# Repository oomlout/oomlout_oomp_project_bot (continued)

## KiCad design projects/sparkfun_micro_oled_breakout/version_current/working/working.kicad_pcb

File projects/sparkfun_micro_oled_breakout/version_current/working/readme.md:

# Micro_OLED_Breakout by sparkfun  
This is a harvested standardized copy of a project from github.  
The original project can be found at:  
https://github.com/sparkfun/Micro_OLED_Breakout  
Please consult that link for additional, details, files, and license information.  
Note: It was auto harvested and if the original repo had more than one board file or anything out of the ordinary the files here are likely not representative.

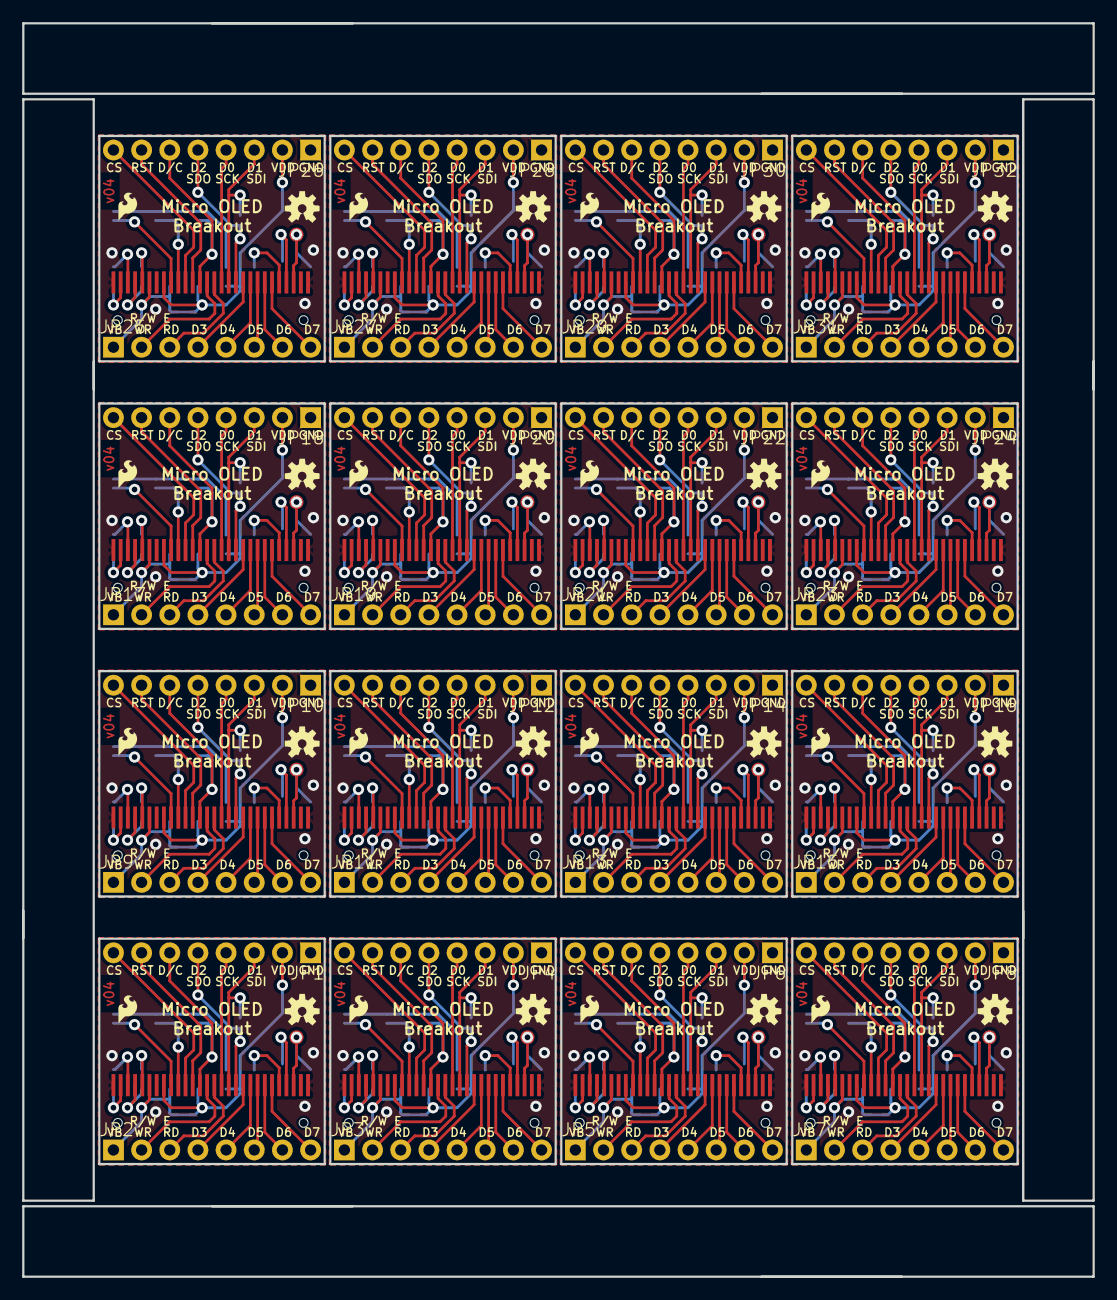
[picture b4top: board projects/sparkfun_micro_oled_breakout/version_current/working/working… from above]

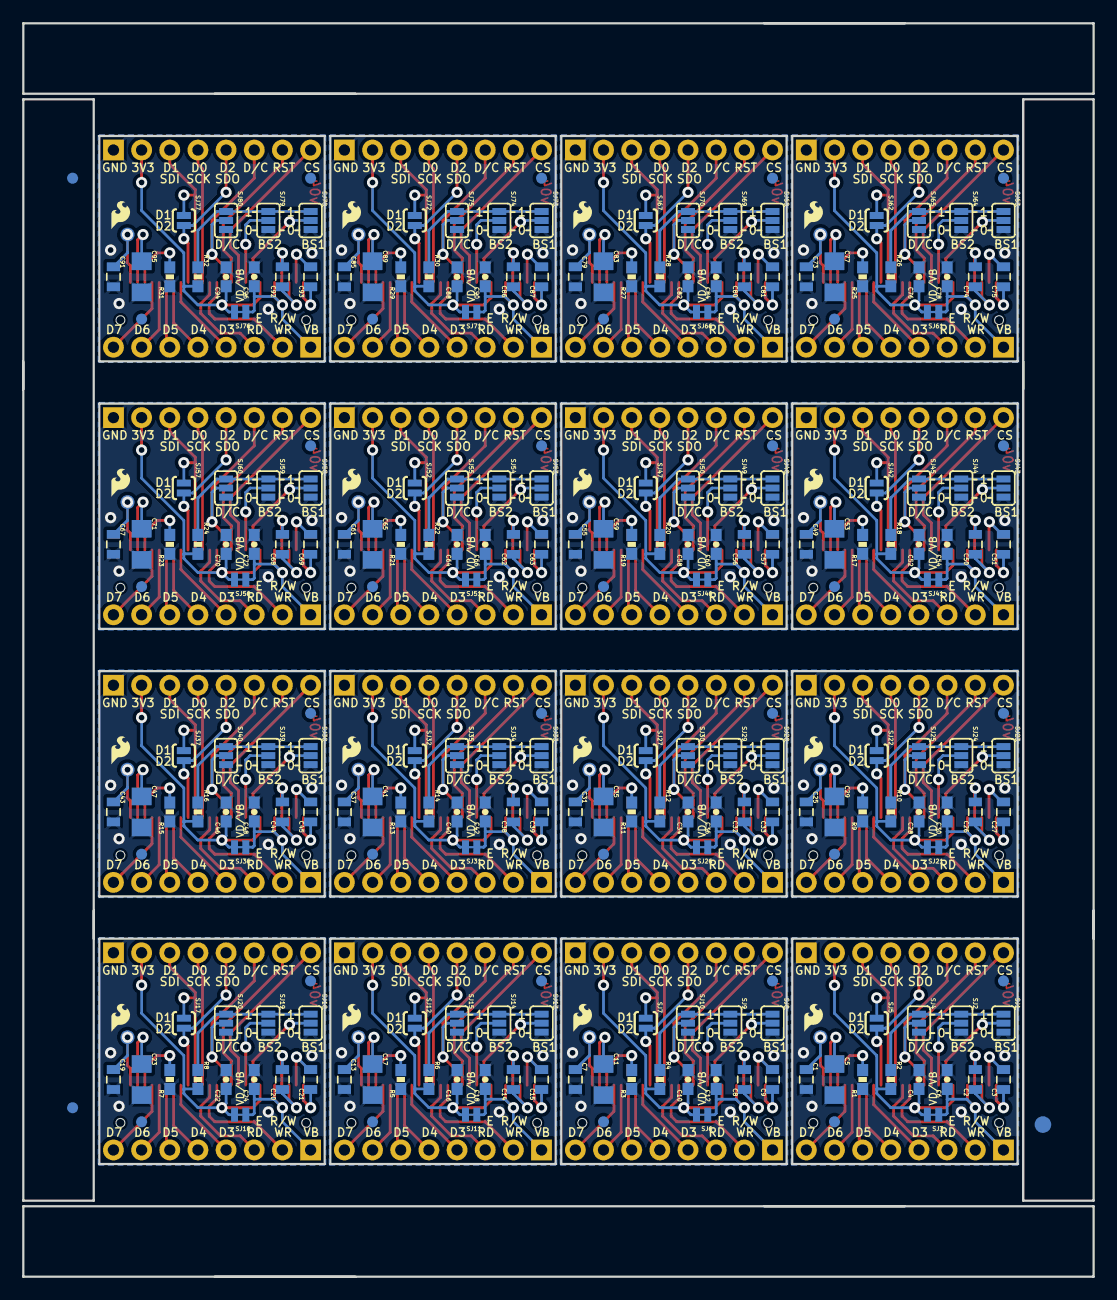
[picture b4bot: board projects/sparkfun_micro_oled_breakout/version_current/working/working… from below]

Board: 2 copper layers, 96.5 x 113.0 mm, 371 parts (275 on the bottom side), 416 nets.

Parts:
C1, C7, C13, C19, C25, C31, C37, C43, C49, C55, C61, C67, C73, C79, C85, C91: 2.2uF; 0805
C2, C3, C8, C9, C14, C15, C20, C21, C26, C27, C32, C33, C38, C39, C44, C45, C50, C51, C56, C57, C62, C63, C68, C69, C74, C75, C80, C81, C86, C87, C92, C93: 1uF X5R; 0805
C4, C6, C10, C12, C16, C18, C22, C24, C28, C30, C34, C36, C40, C42, C46, C48, C52, C54, C58, C60, C64, C66, C70, C72, C76, C78, C82, C84, C88, C90, C94, C96: 1uF; 0603-CAP
C5, C11, C17, C23, C29, C35, C41, C47, C53, C59, C65, C71, C77, C83, C89, C95: 4.7uF/16V; 1206
E$1: FIDUCIAL-1.5X3
E$4, E$8: FIDUCIAL-1X2
FID1, FID2, FID3, FID4, FID5, FID6, FID7, FID8, FID9, FID10, FID11, FID12, FID13, FID14, FID15, FID16, FID17, FID18, FID19, FID20, FID21, FID22, FID23, FID24, FID25, FID26, FID27, FID28, FID29, FID30, FID31, FID32: FIDUCIAL1X2; FIDUCIAL-1X2
JP1, JP2, JP3, JP4, JP5, JP6, JP7, JP8, JP9, JP10, JP11, JP12, JP13, JP14, JP15, JP16, JP17, JP18, JP19, JP20, JP21, JP22, JP23, JP24, JP25, JP26, JP27, JP28, JP29, JP30, JP31, JP32: 1X08_PIN1_NO_SILK
LOGO1, LOGO2, LOGO4, LOGO5, LOGO7, LOGO8, LOGO10, LOGO11, LOGO13, LOGO14, LOGO16, LOGO17, LOGO19, LOGO20, LOGO22, LOGO23, LOGO25, LOGO26, LOGO28, LOGO29, LOGO31, LOGO32, LOGO34, LOGO35, LOGO37, LOGO38, LOGO40, LOGO41, LOGO43, LOGO44, LOGO46, LOGO47: SFE_LOGO_FLAME.1_INCH; SFE_LOGO_FLAME_.1
LOGO3, LOGO6, LOGO9, LOGO12, LOGO15, LOGO18, LOGO21, LOGO24, LOGO27, LOGO30, LOGO33, LOGO36, LOGO39, LOGO42, LOGO45, LOGO48: OSHW-LOGOS; OSHW-LOGO-S
OLED1, OLED2, OLED3, OLED4, OLED5, OLED6, OLED7, OLED8, OLED9, OLED10, OLED11, OLED12, OLED13, OLED14, OLED15, OLED16: OLED0.66; OLED-0.66-64X48
R1, R3, R5, R7, R9, R11, R13, R15, R17, R19, R21, R23, R25, R27, R29, R31: 390k; 0603-RES
R2, R4, R6, R8, R10, R12, R14, R16, R18, R20, R22, R24, R26, R28, R30, R32: 10k; 0603-RES
SJ1, SJ8, SJ13, SJ18, SJ23, SJ28, SJ33, SJ38, SJ43, SJ48, SJ53, SJ58, SJ63, SJ68, SJ73, SJ78: BS1; PAD-JUMPER-3-2OF3_NC_BY_PASTE_YES_SILK_FULL_BOX
SJ2, SJ9, SJ14, SJ19, SJ24, SJ29, SJ34, SJ39, SJ44, SJ49, SJ54, SJ59, SJ64, SJ69, SJ74, SJ79: BS2; PAD-JUMPER-3-2OF3_NC_BY_PASTE_YES_SILK_FULL_BOX
SJ3, SJ6, SJ11, SJ16, SJ21, SJ26, SJ31, SJ36, SJ41, SJ46, SJ51, SJ56, SJ61, SJ66, SJ71, SJ76: PAD-JUMPER-2-NC_BY_TRACE_NO_SILK
SJ4, SJ10, SJ15, SJ20, SJ25, SJ30, SJ35, SJ40, SJ45, SJ50, SJ55, SJ60, SJ65, SJ70, SJ75, SJ80: PAD-JUMPER-3-NO-TIGHT
SJ5, SJ7, SJ12, SJ17, SJ22, SJ27, SJ32, SJ37, SJ42, SJ47, SJ52, SJ57, SJ62, SJ67, SJ72, SJ77: PAD-JUMPER-2-NO_YES_SILK
TP1, TP2, TP3, TP4, TP5, TP6, TP7, TP8, TP9, TP10, TP11, TP12, TP13, TP14, TP15, TP16, TP17, TP18, TP19, TP20, TP21, TP22, TP23, TP24, TP25, TP26, TP27, TP28, TP29, TP30, TP31, TP32: TEST-POINT3X5; PAD.03X.05

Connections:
BS1: OLED1.9, SJ1.2
BS2: OLED1.10, SJ2.2
BS3: OLED2.9, SJ8.2
BS4: OLED2.10, SJ9.2
BS5: OLED3.9, SJ13.2
BS6: OLED3.10, SJ14.2
BS7: OLED4.9, SJ18.2
BS8: OLED4.10, SJ19.2
BS9: OLED5.9, SJ23.2
BS10: OLED5.10, SJ24.2
BS11: OLED6.9, SJ28.2
BS12: OLED6.10, SJ29.2
BS13: OLED7.9, SJ33.2
BS14: OLED7.10, SJ34.2
BS15: OLED8.9, SJ38.2
BS16: OLED8.10, SJ39.2
BS17: OLED9.9, SJ43.2
BS18: OLED9.10, SJ44.2
BS19: OLED10.9, SJ48.2
BS20: OLED10.10, SJ49.2
BS21: OLED11.9, SJ53.2
BS22: OLED11.10, SJ54.2
BS23: OLED12.9, SJ58.2
BS24: OLED12.10, SJ59.2
BS25: OLED13.9, SJ63.2
BS26: OLED13.10, SJ64.2
BS27: OLED14.9, SJ68.2
BS28: OLED14.10, SJ69.2
BS29: OLED15.9, SJ73.2
BS30: OLED15.10, SJ74.2
BS31: OLED16.9, SJ78.2
BS32: OLED16.10, SJ79.2
C1N: C2.2, OLED1.5
C1N1: C8.2, OLED2.5
C1N2: C14.2, OLED3.5
C1N3: C20.2, OLED4.5
C1N4: C26.2, OLED5.5
C1N5: C32.2, OLED6.5
C1N6: C38.2, OLED7.5
C1N7: C44.2, OLED8.5
C1N8: C50.2, OLED9.5
C1N9: C56.2, OLED10.5
C1N10: C62.2, OLED11.5
C1N11: C68.2, OLED12.5
C1N12: C74.2, OLED13.5
C1N13: C80.2, OLED14.5
C1N14: C86.2, OLED15.5
C1N15: C92.2, OLED16.5
C1P: C2.1, OLED1.4
C1P1: C8.1, OLED2.4
C1P2: C14.1, OLED3.4
C1P3: C20.1, OLED4.4
C1P4: C26.1, OLED5.4
C1P5: C32.1, OLED6.4
C1P6: C38.1, OLED7.4
C1P7: C44.1, OLED8.4
C1P8: C50.1, OLED9.4
C1P9: C56.1, OLED10.4
C1P10: C62.1, OLED11.4
C1P11: C68.1, OLED12.4
C1P12: C74.1, OLED13.4
C1P13: C80.1, OLED14.4
C1P14: C86.1, OLED15.4
C1P15: C92.1, OLED16.4
C2N: C3.2, OLED1.3
C2N1: C9.2, OLED2.3
C2N2: C15.2, OLED3.3
C2N3: C21.2, OLED4.3
C2N4: C27.2, OLED5.3
C2N5: C33.2, OLED6.3
C2N6: C39.2, OLED7.3
C2N7: C45.2, OLED8.3
C2N8: C51.2, OLED9.3
C2N9: C57.2, OLED10.3
C2N10: C63.2, OLED11.3
C2N11: C69.2, OLED12.3
C2N12: C75.2, OLED13.3
C2N13: C81.2, OLED14.3
C2N14: C87.2, OLED15.3
C2N15: C93.2, OLED16.3
C2P: C3.1, OLED1.2
C2P1: C9.1, OLED2.2
C2P2: C15.1, OLED3.2
C2P3: C21.1, OLED4.2
C2P4: C27.1, OLED5.2
C2P5: C33.1, OLED6.2
C2P6: C39.1, OLED7.2
C2P7: C45.1, OLED8.2
C2P8: C51.1, OLED9.2
C2P9: C57.1, OLED10.2
C2P10: C63.1, OLED11.2
C2P11: C69.1, OLED12.2
C2P12: C75.1, OLED13.2
C2P13: C81.1, OLED14.2
C2P14: C87.1, OLED15.2
C2P15: C93.1, OLED16.2
CS: JP1.8, OLED1.11
CS1: JP4.8, OLED2.11
CS2: JP6.8, OLED3.11
CS3: JP8.8, OLED4.11
CS4: JP10.8, OLED5.11
CS5: JP12.8, OLED6.11
CS6: JP14.8, OLED7.11
CS7: JP16.8, OLED8.11
CS8: JP18.8, OLED9.11
CS9: JP20.8, OLED10.11
CS10: JP22.8, OLED11.11
CS11: JP24.8, OLED12.11
CS12: JP26.8, OLED13.11
CS13: JP28.8, OLED14.11
CS14: JP30.8, OLED15.11
CS15: JP32.8, OLED16.11
D0/SCK: JP1.4, OLED1.16
D0/SCK1: JP4.4, OLED2.16
D0/SCK2: JP6.4, OLED3.16
D0/SCK3: JP8.4, OLED4.16
D0/SCK4: JP10.4, OLED5.16
D0/SCK5: JP12.4, OLED6.16
D0/SCK6: JP14.4, OLED7.16
D0/SCK7: JP16.4, OLED8.16
D0/SCK8: JP18.4, OLED9.16
D0/SCK9: JP20.4, OLED10.16
D0/SCK10: JP22.4, OLED11.16
D0/SCK11: JP24.4, OLED12.16
D0/SCK12: JP26.4, OLED13.16
D0/SCK13: JP28.4, OLED14.16
D0/SCK14: JP30.4, OLED15.16
D0/SCK15: JP32.4, OLED16.16
D1: JP3.8, OLED2.23
D1/MOSI: JP1.3, OLED1.17, SJ5.1
D1/MOSI1: JP4.3, OLED2.17, SJ7.1
D1/MOSI2: JP6.3, OLED3.17, SJ12.1
D1/MOSI3: JP8.3, OLED4.17, SJ17.1
D1/MOSI4: JP10.3, OLED5.17, SJ22.1
D1/MOSI5: JP12.3, OLED6.17, SJ27.1
D1/MOSI6: JP14.3, OLED7.17, SJ32.1
D1/MOSI7: JP16.3, OLED8.17, SJ37.1
D1/MOSI8: JP18.3, OLED9.17, SJ42.1
D1/MOSI9: JP20.3, OLED10.17, SJ47.1
D1/MOSI10: JP22.3, OLED11.17, SJ52.1
D1/MOSI11: JP24.3, OLED12.17, SJ57.1
D1/MOSI12: JP26.3, OLED13.17, SJ62.1
D1/MOSI13: JP28.3, OLED14.17, SJ67.1
D1/MOSI14: JP30.3, OLED15.17, SJ72.1
D1/MOSI15: JP32.3, OLED16.17, SJ77.1
D2: JP1.5, OLED1.18, SJ5.2
D3: JP2.4, OLED1.19
D4: JP2.5, OLED1.20
D5: JP2.6, OLED1.21
D6: JP2.7, OLED1.22
D7: JP2.8, OLED1.23
D8: JP3.7, OLED2.22
D9: JP3.6, OLED2.21
D10: JP3.5, OLED2.20
D11: JP3.4, OLED2.19
D12: JP4.5, OLED2.18, SJ7.2
D13: JP5.8, OLED3.23
D14: JP5.7, OLED3.22
D15: JP5.6, OLED3.21
D16: JP5.5, OLED3.20
D17: JP5.4, OLED3.19
D18: JP6.5, OLED3.18, SJ12.2
D19: JP7.8, OLED4.23
D20: JP7.7, OLED4.22
D21: JP7.6, OLED4.21
D22: JP7.5, OLED4.20
D23: JP7.4, OLED4.19
D24: JP8.5, OLED4.18, SJ17.2
D25: JP9.8, OLED5.23
D26: JP9.7, OLED5.22
D27: JP9.6, OLED5.21
D28: JP9.5, OLED5.20
D29: JP9.4, OLED5.19
D30: JP10.5, OLED5.18, SJ22.2
D31: JP11.8, OLED6.23
D32: JP11.7, OLED6.22
D33: JP11.6, OLED6.21
D34: JP11.5, OLED6.20
D35: JP11.4, OLED6.19
D36: JP12.5, OLED6.18, SJ27.2
D37: JP13.8, OLED7.23
D38: JP13.7, OLED7.22
D39: JP13.6, OLED7.21
D40: JP13.5, OLED7.20
D41: JP13.4, OLED7.19
D42: JP14.5, OLED7.18, SJ32.2
D43: JP15.8, OLED8.23
D44: JP15.7, OLED8.22
D45: JP15.6, OLED8.21
D46: JP15.5, OLED8.20
D47: JP15.4, OLED8.19
D48: JP16.5, OLED8.18, SJ37.2
D49: JP17.8, OLED9.23
D50: JP17.7, OLED9.22
D51: JP17.6, OLED9.21
D52: JP17.5, OLED9.20
D53: JP17.4, OLED9.19
D54: JP18.5, OLED9.18, SJ42.2
D55: JP19.8, OLED10.23
D56: JP19.7, OLED10.22
D57: JP19.6, OLED10.21
D58: JP19.5, OLED10.20
D59: JP19.4, OLED10.19
D60: JP20.5, OLED10.18, SJ47.2
D61: JP21.8, OLED11.23
D62: JP21.7, OLED11.22
D63: JP21.6, OLED11.21
D64: JP21.5, OLED11.20
D65: JP21.4, OLED11.19
D66: JP22.5, OLED11.18, SJ52.2
D67: JP23.8, OLED12.23
D68: JP23.7, OLED12.22
D69: JP23.6, OLED12.21
D70: JP23.5, OLED12.20
D71: JP23.4, OLED12.19
D72: JP24.5, OLED12.18, SJ57.2
D73: JP25.8, OLED13.23
D74: JP25.7, OLED13.22
D75: JP25.6, OLED13.21
D76: JP25.5, OLED13.20
D77: JP25.4, OLED13.19
D78: JP26.5, OLED13.18, SJ62.2
D79: JP27.8, OLED14.23
D80: JP27.7, OLED14.22
D81: JP27.6, OLED14.21
D82: JP27.5, OLED14.20
D83: JP27.4, OLED14.19
D84: JP28.5, OLED14.18, SJ67.2
D85: JP29.8, OLED15.23
D86: JP29.7, OLED15.22
D87: JP29.6, OLED15.21
D88: JP29.5, OLED15.20
D89: JP29.4, OLED15.19
D90: JP30.5, OLED15.18, SJ72.2
D91: JP31.8, OLED16.23
D92: JP31.7, OLED16.22
D93: JP31.6, OLED16.21
D94: JP31.5, OLED16.20
D95: JP31.4, OLED16.19
D96: JP32.5, OLED16.18, SJ77.2
D/C: JP1.6, OLED1.13, SJ4.2
D/C1: JP4.6, OLED2.13, SJ10.2
D/C2: JP6.6, OLED3.13, SJ15.2
D/C3: JP8.6, OLED4.13, SJ20.2
D/C4: JP10.6, OLED5.13, SJ25.2
D/C5: JP12.6, OLED6.13, SJ30.2
D/C6: JP14.6, OLED7.13, SJ35.2
D/C7: JP16.6, OLED8.13, SJ40.2
D/C8: JP18.6, OLED9.13, SJ45.2
D/C9: JP20.6, OLED10.13, SJ50.2
D/C10: JP22.6, OLED11.13, SJ55.2
D/C11: JP24.6, OLED12.13, SJ60.2
D/C12: JP26.6, OLED13.13, SJ65.2
D/C13: JP28.6, OLED14.13, SJ70.2
D/C14: JP30.6, OLED15.13, SJ75.2
D/C15: JP32.6, OLED16.13, SJ80.2
GND: C1.2, C4.2, C5.2, C6.2, JP1.1, OLED1.1, OLED1.7, OLED1.27, OLED1.28, R1.1, SJ1.3, SJ2.3, SJ4.3
GND1: C7.2, C10.2, C11.2, C12.2, JP4.1, OLED2.1, OLED2.7, OLED2.27, OLED2.28, R3.1, SJ8.3, SJ9.3, SJ10.3
GND2: C13.2, C16.2, C17.2, C18.2, JP6.1, OLED3.1, OLED3.7, OLED3.27, OLED3.28, R5.1, SJ13.3, SJ14.3, SJ15.3
GND3: C19.2, C22.2, C23.2, C24.2, JP8.1, OLED4.1, OLED4.7, OLED4.27, OLED4.28, R7.1, SJ18.3, SJ19.3, SJ20.3
GND4: C25.2, C28.2, C29.2, C30.2, JP10.1, OLED5.1, OLED5.7, OLED5.27, OLED5.28, R9.1, SJ23.3, SJ24.3, SJ25.3
GND5: C31.2, C34.2, C35.2, C36.2, JP12.1, OLED6.1, OLED6.7, OLED6.27, OLED6.28, R11.1, SJ28.3, SJ29.3, SJ30.3
GND6: C37.2, C40.2, C41.2, C42.2, JP14.1, OLED7.1, OLED7.7, OLED7.27, OLED7.28, R13.1, SJ33.3, SJ34.3, SJ35.3
GND7: C43.2, C46.2, C47.2, C48.2, JP16.1, OLED8.1, OLED8.7, OLED8.27, OLED8.28, R15.1, SJ38.3, SJ39.3, SJ40.3
GND8: C49.2, C52.2, C53.2, C54.2, JP18.1, OLED9.1, OLED9.7, OLED9.27, OLED9.28, R17.1, SJ43.3, SJ44.3, SJ45.3
GND9: C55.2, C58.2, C59.2, C60.2, JP20.1, OLED10.1, OLED10.7, OLED10.27, OLED10.28, R19.1, SJ48.3, SJ49.3, SJ50.3
GND10: C61.2, C64.2, C65.2, C66.2, JP22.1, OLED11.1, OLED11.7, OLED11.27, OLED11.28, R21.1, SJ53.3, SJ54.3, SJ55.3
GND11: C67.2, C70.2, C71.2, C72.2, JP24.1, OLED12.1, OLED12.7, OLED12.27, OLED12.28, R23.1, SJ58.3, SJ59.3, SJ60.3
GND12: C73.2, C76.2, C77.2, C78.2, JP26.1, OLED13.1, OLED13.7, OLED13.27, OLED13.28, R25.1, SJ63.3, SJ64.3, SJ65.3
GND13: C79.2, C82.2, C83.2, C84.2, JP28.1, OLED14.1, OLED14.7, OLED14.27, OLED14.28, R27.1, SJ68.3, SJ69.3, SJ70.3
GND14: C85.2, C88.2, C89.2, C90.2, JP30.1, OLED15.1, OLED15.7, OLED15.27, OLED15.28, R29.1, SJ73.3, SJ74.3, SJ75.3
GND15: C91.2, C94.2, C95.2, C96.2, JP32.1, OLED16.1, OLED16.7, OLED16.27, OLED16.28, R31.1, SJ78.3, SJ79.3, SJ80.3
IREF: OLED1.24, R1.2
IREF1: OLED2.24, R3.2
IREF2: OLED3.24, R5.2
IREF3: OLED4.24, R7.2
IREF4: OLED5.24, R9.2
IREF5: OLED6.24, R11.2
IREF6: OLED7.24, R13.2
IREF7: OLED8.24, R15.2
IREF8: OLED9.24, R17.2
IREF9: OLED10.24, R19.2
IREF10: OLED11.24, R21.2
IREF11: OLED12.24, R23.2
IREF12: OLED13.24, R25.2
IREF13: OLED14.24, R27.2
IREF14: OLED15.24, R29.2
IREF15: OLED16.24, R31.2
RD/E: JP2.3, OLED1.15
RD/E1: JP3.3, OLED2.15
RD/E2: JP5.3, OLED3.15
RD/E3: JP7.3, OLED4.15
RD/E4: JP9.3, OLED5.15
RD/E5: JP11.3, OLED6.15
RD/E6: JP13.3, OLED7.15
RD/E7: JP15.3, OLED8.15
RD/E8: JP17.3, OLED9.15
RD/E9: JP19.3, OLED10.15
RD/E10: JP21.3, OLED11.15
RD/E11: JP23.3, OLED12.15
RD/E12: JP25.3, OLED13.15
RD/E13: JP27.3, OLED14.15
RD/E14: JP29.3, OLED15.15
RD/E15: JP31.3, OLED16.15
RESET: JP1.7, OLED1.12
RESET1: JP4.7, OLED2.12
RESET2: JP6.7, OLED3.12
RESET3: JP8.7, OLED4.12
RESET4: JP10.7, OLED5.12
RESET5: JP12.7, OLED6.12
RESET6: JP14.7, OLED7.12
RESET7: JP16.7, OLED8.12
RESET8: JP18.7, OLED9.12
RESET9: JP20.7, OLED10.12
RESET10: JP22.7, OLED11.12
RESET11: JP24.7, OLED12.12
RESET12: JP26.7, OLED13.12
RESET13: JP28.7, OLED14.12
RESET14: JP30.7, OLED15.12
RESET15: JP32.7, OLED16.12
VBAT: C6.1, JP2.1, OLED1.6, SJ3.1
VBAT1: C12.1, JP3.1, OLED2.6, SJ6.1
VBAT2: C18.1, JP5.1, OLED3.6, SJ11.1
VBAT3: C24.1, JP7.1, OLED4.6, SJ16.1
VBAT4: C30.1, JP9.1, OLED5.6, SJ21.1
VBAT5: C36.1, JP11.1, OLED6.6, SJ26.1
VBAT6: C42.1, JP13.1, OLED7.6, SJ31.1
VBAT7: C48.1, JP15.1, OLED8.6, SJ36.1
VBAT8: C54.1, JP17.1, OLED9.6, SJ41.1
VBAT9: C60.1, JP19.1, OLED10.6, SJ46.1
VBAT10: C66.1, JP21.1, OLED11.6, SJ51.1
VBAT11: C72.1, JP23.1, OLED12.6, SJ56.1
VBAT12: C78.1, JP25.1, OLED13.6, SJ61.1
VBAT13: C84.1, JP27.1, OLED14.6, SJ66.1
VBAT14: C90.1, JP29.1, OLED15.6, SJ71.1
VBAT15: C96.1, JP31.1, OLED16.6, SJ76.1
VCC: C1.1, OLED1.26, TP1.P$1, TP2.P$1
VCC1: C7.1, OLED2.26, TP3.P$1, TP4.P$1
VCC2: C13.1, OLED3.26, TP5.P$1, TP6.P$1
VCC3: C19.1, OLED4.26, TP7.P$1, TP8.P$1
VCC4: C25.1, OLED5.26, TP9.P$1, TP10.P$1
VCC5: C31.1, OLED6.26, TP11.P$1, TP12.P$1
VCC6: C37.1, OLED7.26, TP13.P$1, TP14.P$1
VCC7: C43.1, OLED8.26, TP15.P$1, TP16.P$1
VCC8: C49.1, OLED9.26, TP17.P$1, TP18.P$1
VCC9: C55.1, OLED10.26, TP19.P$1, TP20.P$1
VCC10: C61.1, OLED11.26, TP21.P$1, TP22.P$1
VCC11: C67.1, OLED12.26, TP23.P$1, TP24.P$1
VCC12: C73.1, OLED13.26, TP25.P$1, TP26.P$1
VCC13: C79.1, OLED14.26, TP27.P$1, TP28.P$1
VCC14: C85.1, OLED15.26, TP29.P$1, TP30.P$1
VCC15: C91.1, OLED16.26, TP31.P$1, TP32.P$1
VCOMH: C5.1, OLED1.25
VCOMH1: C11.1, OLED2.25
VCOMH2: C17.1, OLED3.25
VCOMH3: C23.1, OLED4.25
VCOMH4: C29.1, OLED5.25
VCOMH5: C35.1, OLED6.25
VCOMH6: C41.1, OLED7.25
VCOMH7: C47.1, OLED8.25
VCOMH8: C53.1, OLED9.25
VCOMH9: C59.1, OLED10.25
VCOMH10: C65.1, OLED11.25
VCOMH11: C71.1, OLED12.25
VCOMH12: C77.1, OLED13.25
VCOMH13: C83.1, OLED14.25
VCOMH14: C89.1, OLED15.25
VCOMH15: C95.1, OLED16.25
VDD: C4.1, JP1.2, OLED1.8, R2.2, SJ3.2
VDD1: C10.1, JP4.2, OLED2.8, R4.2, SJ6.2
VDD2: C16.1, JP6.2, OLED3.8, R6.2, SJ11.2
VDD3: C22.1, JP8.2, OLED4.8, R8.2, SJ16.2
VDD4: C28.1, JP10.2, OLED5.8, R10.2, SJ21.2
VDD5: C34.1, JP12.2, OLED6.8, R12.2, SJ26.2
VDD6: C40.1, JP14.2, OLED7.8, R14.2, SJ31.2
VDD7: C46.1, JP16.2, OLED8.8, R16.2, SJ36.2
VDD8: C52.1, JP18.2, OLED9.8, R18.2, SJ41.2
VDD9: C58.1, JP20.2, OLED10.8, R20.2, SJ46.2
VDD10: C64.1, JP22.2, OLED11.8, R22.2, SJ51.2
VDD11: C70.1, JP24.2, OLED12.8, R24.2, SJ56.2
VDD12: C76.1, JP26.2, OLED13.8, R26.2, SJ61.2
VDD13: C82.1, JP28.2, OLED14.8, R28.2, SJ66.2
VDD14: C88.1, JP30.2, OLED15.8, R30.2, SJ71.2
VDD15: C94.1, JP32.2, OLED16.8, R32.2, SJ76.2
VDD_PU: R2.1, SJ1.1, SJ2.1, SJ4.1
VDD_PU1: R4.1, SJ8.1, SJ9.1, SJ10.1
VDD_PU2: R6.1, SJ13.1, SJ14.1, SJ15.1
VDD_PU3: R8.1, SJ18.1, SJ19.1, SJ20.1
VDD_PU4: R10.1, SJ23.1, SJ24.1, SJ25.1
VDD_PU5: R12.1, SJ28.1, SJ29.1, SJ30.1
VDD_PU6: R14.1, SJ33.1, SJ34.1, SJ35.1
VDD_PU7: R16.1, SJ38.1, SJ39.1, SJ40.1
VDD_PU8: R18.1, SJ43.1, SJ44.1, SJ45.1
VDD_PU9: R20.1, SJ48.1, SJ49.1, SJ50.1
VDD_PU10: R22.1, SJ53.1, SJ54.1, SJ55.1
VDD_PU11: R24.1, SJ58.1, SJ59.1, SJ60.1
VDD_PU12: R26.1, SJ63.1, SJ64.1, SJ65.1
VDD_PU13: R28.1, SJ68.1, SJ69.1, SJ70.1
VDD_PU14: R30.1, SJ73.1, SJ74.1, SJ75.1
VDD_PU15: R32.1, SJ78.1, SJ79.1, SJ80.1
WR/RW: JP2.2, OLED1.14
WR/RW1: JP3.2, OLED2.14
WR/RW2: JP5.2, OLED3.14
WR/RW3: JP7.2, OLED4.14
WR/RW4: JP9.2, OLED5.14
WR/RW5: JP11.2, OLED6.14
WR/RW6: JP13.2, OLED7.14
WR/RW7: JP15.2, OLED8.14
WR/RW8: JP17.2, OLED9.14
WR/RW9: JP19.2, OLED10.14
WR/RW10: JP21.2, OLED11.14
WR/RW11: JP23.2, OLED12.14
WR/RW12: JP25.2, OLED13.14
WR/RW13: JP27.2, OLED14.14
WR/RW14: JP29.2, OLED15.14
WR/RW15: JP31.2, OLED16.14

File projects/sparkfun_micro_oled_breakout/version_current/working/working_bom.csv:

"Id";"Designator";"Footprint";"Quantity";"Designation";"Supplier and ref";
1;"TP28,TP22,TP20,TP2,TP12,TP6,TP26,TP30,TP32,TP14,TP10,TP24,TP16,TP4,TP18,TP8,TP13,TP9,TP1,TP17,TP5,TP3,TP31,TP15,TP21,TP29,TP7,TP23,TP25,TP27,TP11,TP19";"PAD.03X.05";32;"TEST-POINT3X5";;;
2;"LOGO27,LOGO3,LOGO6,LOGO39,LOGO21,LOGO18,LOGO9,LOGO36,LOGO45,LOGO30,LOGO33,LOGO24,LOGO42,LOGO48,LOGO12,LOGO15";"OSHW-LOGO-S";16;"OSHW-LOGOS";;;
3;"JP15,JP4,JP10,JP8,JP29,JP14,JP18,JP23,JP31,JP22,JP3,JP2,JP21,JP24,JP1,JP32,JP11,JP30,JP9,JP16,JP7,JP28,JP13,JP27,JP5,JP12,JP19,JP25,JP20,JP26,JP17,JP6";"1X08_PIN1_NO_SILK";32;"";;;
4;"OLED11,OLED5,OLED7,OLED14,OLED6,OLED4,OLED16,OLED3,OLED2,OLED15,OLED8,OLED10,OLED1,OLED9,OLED12,OLED13";"OLED-0.66-64X48";16;"OLED0.66";;;
5;"LOGO37,LOGO13,LOGO31,LOGO1,LOGO7,LOGO34,LOGO43,LOGO10,LOGO28,LOGO22,LOGO19,LOGO40,LOGO16,LOGO25,LOGO46,LOGO2,LOGO32,LOGO14,LOGO47,LOGO11,LOGO20,LOGO17,LOGO4,LOGO41,LOGO35,LOGO29,LOGO23,LOGO26,LOGO8,LOGO44,LOGO38,LOGO5";"SFE_LOGO_FLAME_.1";32;"SFE_LOGO_FLAME.1_INCH";;;
6;"C66,C6,C36,C48,C90,C60,C46,C96,C70,C30,C40,C76,C78,C4,C58,C12,C84,C34,C82,C18,C72,C28,C54,C94,C22,C16,C52,C24,C42,C64,C10,C88";"0603-CAP";32;"1uF";;;
7;"SJ22,SJ5,SJ67,SJ77,SJ17,SJ72,SJ42,SJ27,SJ12,SJ32,SJ62,SJ52,SJ47,SJ37,SJ57,SJ7";"PAD-JUMPER-2-NO_YES_SILK";16;"";;;
8;"C11,C35,C89,C53,C59,C95,C41,C65,C29,C17,C83,C77,C71,C47,C23,C5";"1206";16;"4.7uF/16V";;;
9;"SJ50,SJ20,SJ40,SJ60,SJ55,SJ4,SJ45,SJ25,SJ15,SJ10,SJ80,SJ70,SJ35,SJ30,SJ75,SJ65";"PAD-JUMPER-3-NO-TIGHT";16;"";;;
10;"E$1";"FIDUCIAL-1.5X3";1;"";;;
11;"SJ59,SJ74,SJ39,SJ79,SJ64,SJ44,SJ14,SJ2,SJ24,SJ49,SJ19,SJ54,SJ29,SJ9,SJ34,SJ69";"PAD-JUMPER-3-2OF3_NC_BY_PASTE_YES_SILK_FULL_BOX";16;"BS2";;;
12;"R12,R24,R30,R8,R14,R28,R6,R20,R22,R18,R26,R10,R16,R4,R2,R32";"0603-RES";16;"10k";;;
13;"C39,C63,C32,C93,C74,C92,C38,C68,C69,C87,C20,C2,C57,C8,C45,C56,C14,C15,C9,C27,C3,C26,C44,C33,C51,C81,C50,C62,C86,C21,C80,C75";"0805";32;"1uF X5R";;;
14;"SJ33,SJ63,SJ23,SJ1,SJ8,SJ13,SJ68,SJ28,SJ48,SJ38,SJ78,SJ73,SJ53,SJ18,SJ43,SJ58";"PAD-JUMPER-3-2OF3_NC_BY_PASTE_YES_SILK_FULL_BOX";16;"BS1";;;
15;"FID28,FID30,FID14,FID17,FID18,FID15,FID31,FID24,FID11,FID3,FID26,FID29,FID1,FID19,FID6,FID8,FID23,FID12,FID9,FID7,FID10,FID25,FID22,FID16,FID27,FID32,FID2,FID5,FID21,FID20,FID13,FID4";"FIDUCIAL-1X2";32;"FIDUCIAL1X2";;;
16;"SJ71,SJ11,SJ21,SJ61,SJ41,SJ3,SJ6,SJ76,SJ26,SJ31,SJ16,SJ36,SJ56,SJ46,SJ66,SJ51";"PAD-JUMPER-2-NC_BY_TRACE_NO_SILK";16;"";;;
17;"R29,R5,R3,R19,R27,R23,R7,R9,R17,R1,R25,R21,R15,R13,R31,R11";"0603-RES";16;"390k";;;
18;"C13,C91,C49,C67,C61,C19,C73,C31,C25,C1,C85,C43,C37,C79,C55,C7";"0805";16;"2.2uF";;;
19;"E$8,E$4";"FIDUCIAL-1X2";2;"";;;
